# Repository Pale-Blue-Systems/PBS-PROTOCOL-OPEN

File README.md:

# Pale Blue Systems – Open Communication Standards

This repository contains the **open communication standards stewarded by the Pale Blue Systems Foundation (PBSF)**: the PBS protocol specifications, their conformance profiles, the governance documents, and the alignment and traceability records that relate PBS to external sources.

The standards in this repository define a shared **mission-semantic interoperability language** that allows spacecraft, rovers, habitats, autonomous systems, and ground applications to preserve mission meaning, authority, service intent, priority, freshness, security requirements, and PNT context across heterogeneous networks and independently operated service providers.

The PBS specifications define a fixed 44-byte message envelope and a set of optional extensions. Together they carry mission semantics with the data: source identity, priority, timestamp and lifetime, Service Intent, authority context, security profile and PNT context. The specifications define the same semantics over IP, BPv7 and mission-specific links and across independently operated service providers.

---

## Context and Intent

Pale Blue Systems publishes these standards in anticipation of a future space environment that includes **multiple space agencies, commercial operators, scientific missions, private infrastructure, and long-lived off-Earth systems operating concurrently**.

PBS addresses an operating environment in which space agencies, commercial operators and science missions run independently built systems that exchange data over shared relays and networks. For the Moon, the LunaNet Interoperability Specification (LNIS V005, NASA, ESA and JAXA, 29 January 2025) describes LunaNet as a network of cooperating networks on which LunaNet Service Providers deliver communications, PNT and other services, and expects user needs to be met by a combination of interoperable providers (LNIS V005 Preface and Section 1).

This repository establishes a durable mission-semantic interoperability standard for the multi-provider lunar, cislunar, planetary, and deep-space operating environment. It makes interoperability, authority, service intent, and coordination requirements **explicit and addressable early**, before architectural assumptions become embedded in deployed infrastructure.

Additional context on why this work is published now, and the long-term architectural motivations behind it, is available in [`WHY-NOW.md`](WHY-NOW.md).

---

## Why This Repository Exists

As space operations move toward sustained lunar presence, cislunar infrastructure, and Mars exploration, missions increasingly depend on distributed systems operating across:

- long and variable communication delays
- intermittent or scheduled connectivity
- multiple independent authorities and vendors
- human-rated, safety-critical environments

Under these conditions, data must be stored and forwarded between contacts, and its meaning, priority and authority must survive the transfer between organizations.

Strategic analysis has formally identified communications, networking, and coordination as critical technology shortfalls for future exploration architectures, including the need for systems that operate reliably across deep-space and planetary environments.

PBSF exists to steward open standards that directly address these conditions.

NASA's *FY26 Civil Space Shortfall Prioritization* (Space Technology Mission Directorate, May 2026) includes four need statements that PBS v1.4 traces to:

| Need ID | Need statement |
|---|---|
| 13.09 | “Provide advanced networking needed for multi-spacecraft responsive space operations.” |
| 15.01 | “Provide scalable, reliable surface-to-surface communications between assets on the lunar surface that is usable by all participating elements.” |
| 15.03 | “Achieve safe, efficient human-robot interactions for exploration missions, secure command and control over high-latency, bandwidth-limited networks, or implement reliable automated safing sequences.” |
| 24.05 | “Develop a lunar position, navigation, and timing architecture capable of scaling to long term operational needs.” |

Source: <https://www.nasa.gov/wp-content/uploads/2026/05/fy26-civil-space-shortfall-prioritization.pdf>. The requirements PBS derives from them are in [`PBS-TRACE-NASA-FY26-01`](PBS-ALIGNMENT-LIB/PBS-TRACE-NASA-FY26-01.md).

---

## What This Repository Contains

### Specifications

[`PBS-RFC-LIB/`](PBS-RFC-LIB/) contains 19 specifications. PBS Core comprises four specifications with Status Core. A PBS Core conformant implementation implements PBS-ENV-01, PBS-PRIO-01 and PBS-SEC-A-01 (PBS-CONFORMANCE-01 Section 3) and meets the further MUST requirements of PBS-CONFORMANCE-01 Sections 4–9 and 12. The remaining specifications are optional extensions, interoperability and conformance profiles, and governance.

### Reference Implementation

The PBS_LINK Python SDK (<https://github.com/Pale-Blue-Systems/PBS_LINK>, distribution `pbs-link` 0.1.3, import package `PBS_LINK`) implements the PBS-ENV-01 v1.3 envelope. It is maintained in its own repository.

### Hardware Reference Designs

[`PBS-HW-LIB/`](PBS-HW-LIB/) holds open reference designs for hardware that carries PBS traffic: a swappable surface communication module (PBS-HW-SCM-01) and a master device identity tag that can be fitted to any unit (PBS-HW-ID-01). They are informational and do not affect PBS conformance.

### Governance and Alignment

[`PBS-OPEN-STANDARD.md`](PBS-OPEN-STANDARD.md) and [`PBS-GOV-01`](PBS-RFC-LIB/PBS-GOV-01.md) define the stewardship and change process. [`PBS-ALIGNMENT-LIB/`](PBS-ALIGNMENT-LIB/) holds the alignment documents and the NASA FY26 traceability matrix.

---

## Architectural Context

PBS operates at the boundary between mission applications and network services.

```text
Mission Applications
(Rovers, Landers, Habitats, Robots, Ops Software)
          │
          ▼
Pale Blue Systems Open Standards
(Mission Semantics, Service Intent, Authority,
 Security Requirements, PNT Context)
          │
          ▼
Interoperable Network Services
(LunaNet, IP, BPv7, BPSec, CCSDS)
          │
          ▼
Provider / Link Infrastructure
(LNSPs, Relays, RF, Optical, 3GPP, Wi-Fi, Ground)
```

PBS envelopes are user-application data to the network services below them (PBS-LNIS-01 Section 2). PBS-LNIS-REQ-007 requires provider transitions to preserve Source ID, authority context, priority, Service Intent and protected application payload.

---

## Relationship to DTN and BPv7

PBS operates over IP, over BPv7, or through a gateway that selects between them (PBS-LNIS-01 Sections 2 and 4). Two optional specifications define carriage over BPv7. Neither supersedes the other. PBS-DTN-MAP-01 references PBS-DTN-MAP-02 Section 4 for the lifetime bound and Section 5 for the mapping profile of priority-based network treatment.

- **PBS-DTN-MAP-01** (v1.5) defines a gateway translation between PBS-native domains and DTN domains. Each PBS envelope maps to exactly one bundle (Section 5.1). The complete envelope, 44-byte header and payload, is placed unmodified in a single BPv7 payload block (Section 6.2). The bundle lifetime does not exceed the time remaining until the envelope expires, and an envelope with TTL 0 takes the gateway's documented no-expiry lifetime unless a PBS-DTN-MAP-02 Section 4 finite limit applies (Sections 6.1 and 6.1.1). The gateway's bundle protocol agent assigns the creation timestamp (Section 6.1). No primary block field carries priority; a gateway that requests network treatment covers all five priority classes and documents the mechanism in a mapping profile (Section 6.3). Source IDs map deterministically to endpoint identifiers (Section 8).
- **PBS-DTN-MAP-02** (v1.5) defines carriage of v1.4 mission semantics over BPv7 for gateways and endpoints. One PBS protocol data unit SHOULD map to one BP application data unit (Section 2). Bundle lifetime SHALL be bounded by the remaining PBS deadline or expiry; when no finite limit applies it is the no-expiry lifetime documented in the mapping profile (Section 4). The adapter preserves PBS priority unchanged; network treatment is selected through BP QoS mechanisms and provider policy (Section 5). Section 6 maps Service Intent values to BPv7 adapter behavior.

PBS-CONFORMANCE-01 Section 3.1 lists both PBS-DTN-MAP-01 and PBS-DTN-MAP-02 as optional. PBS-ENV-01, PBS-ADDR-01 and PBS-ROUTE-01 reference PBS-DTN-MAP-01. PBS-DTN-MAP-01, PBS-SVC-01, PBS-SEC-B-01, PBS-LNIS-01, PBS-QOS-MAP-01, PBS-CONFORMANCE-02 and the NASA FY26 traceability matrix reference PBS-DTN-MAP-02.

---

## External Alignment

Each alignment document identifies its external sources, summarizes what they state, and maps those statements to PBS specification sections. No source names PBS, and no alignment claims endorsement.

| Alignment ID | Source | Identifier |
| :--- | :--- | :--- |
| [PBS-ALIGN-NASA-LCRNS-02](PBS-ALIGNMENT-LIB/PBS-ALIGN-NASA-LCRNS-02.md) | NASA STMD, *FY26 Civil Space Shortfall Prioritization* (2026); NASA, ESA and JAXA, *LunaNet Interoperability Specification*, V005 (2025) | [FY26 PDF](https://www.nasa.gov/wp-content/uploads/2026/05/fy26-civil-space-shortfall-prioritization.pdf), [LNIS V005 PDF](https://www.nasa.gov/wp-content/uploads/2025/02/lunanet-interoperability-specification-v5-baseline.pdf) |
| [PBS-ALIGN-NASA-LCRNS-01](PBS-ALIGNMENT-LIB/PBS-ALIGN-NASA-LCRNS-01.md) | Esper, Heckler, Verville and Ryden, “NASA’s Lunar Communications Relay and Navigation Systems (LCRNS)”, SpaceOps 2025 | [NTRS 20250003321](https://ntrs.nasa.gov/citations/20250003321) |
| [PBS-ALIGN-IEEE-AEROCONF-ONBOARD-2025-01](PBS-ALIGNMENT-LIB/PBS-ALIGN-IEEE-AEROCONF-ONBOARD-2025-01.md) | Verville and Eddy, “Onboard Processing for LunaNet Data Services”, 2025 IEEE Aerospace Conference | doi:10.1109/AERO63441.2025.11068727 |
| [PBS-ALIGN-IEEE-AEROCONF-2025-01](PBS-ALIGNMENT-LIB/PBS-ALIGN-IEEE-AEROCONF-2025-01.md) | Templin et al., “High Performance DTN Using Larger Packets and Kernel Resident Convergence Layers”, 2025 IEEE Aerospace Conference | doi:10.1109/AERO63441.2025.11068517 |
| [PBS-ALIGN-CARBONARA-TNTN-01](PBS-ALIGNMENT-LIB/PBS-ALIGN-CARBONARA-TNTN-01.md) | Carbonara et al., “Hands-On Solutions for Testing Integrated Terrestrial and Non-Terrestrial Networks: A Comprehensive Survey”, *IEEE Open Journal of the Communications Society*, 2025 | doi:10.1109/OJCOMS.2025.3646364 |
| [PBS-ALIGN-NTONTIN-6G-01](PBS-ALIGNMENT-LIB/PBS-ALIGN-NTONTIN-6G-01.md) | Ntontin et al., “A Vision, Survey, and Roadmap Toward Space Communications in the 6G and Beyond Era”, *Proceedings of the IEEE*, 2025 | doi:10.1109/JPROC.2024.3512934 |
| [PBS-ALIGN-SPJ-LEO-2022-01](PBS-ALIGNMENT-LIB/PBS-ALIGN-SPJ-LEO-2022-01.md) | Zhang et al., “LEO Mega Constellations: Review of Development, Impact, Surveillance, and Governance”, *Space: Science & Technology*, 2022 | doi:10.34133/2022/9865174 |
| [PBS-ALIGN-TF-GOVERNANCE-2024-01](PBS-ALIGNMENT-LIB/PBS-ALIGN-TF-GOVERNANCE-2024-01.md) | Beaumier, Couette and Morin, “Hybrid Organisations and Governance Systems: The Case of the European Space Agency”, *Journal of European Public Policy*, 2025 | doi:10.1080/13501763.2024.2325647 |

[PBS-ALIGN-INDEX-01](PBS-ALIGNMENT-LIB/PBS-ALIGN-INDEX-01.md) summarizes each alignment. [PBS-TRACE-NASA-FY26-01](PBS-ALIGNMENT-LIB/PBS-TRACE-NASA-FY26-01.md) traces 19 PBS requirements to the FY26 need statements, LNIS V005 and RFC 9171.

---

## External Alignment & Validation

The Pale Blue Systems Open Standard is explicitly aligned with authoritative, peer-reviewed architectures from major space agencies and technical bodies.

| Alignment ID | External Source | Domain |
| :--- | :--- | :--- |
| **PBS-ALIGN-NASA-LCRNS-01** | NASA LCRNS (Esper, 2025) | Lunar & Cislunar Networking |
| **PBS-ALIGN-IEEE-AEROCONF-2025** | IEEE Aerospace Conference | Space Network Architecture |
| **PBS-ALIGN-IEEE-TNTN-2025** | IEEE ComSoc | Integrated T/NTN Networks |

---

## Open Standards and Stewardship

PBSF is intentionally structured as a neutral foundation stewarding open standards and reference specifications.

- The specifications are public under the Apache License 2.0.
- PBS-GOV-01 Sections 2 and 3 separate stewardship of the specifications from commercial implementation.
- Changes to PBS Core follow the RFC lifecycle of PBS-GOV-01 Section 5. A backward-incompatible change requires a new major version, except a corrective change, which leaves the wire format unchanged and is released in a patch or minor version with migration guidance where needed (PBS-GOV-01 Sections 5.2 and 6).
- Implementations may extend PBS above the protocol layer. Proprietary extensions are not PBS Core (PBS-GOV-01 Section 7).
- Commercial products and mission systems may implement or extend the standards without altering the core language.

This model enables adoption across civil, commercial, and international space programs while allowing innovation and competition above the protocol layer.

---

## Repository Structure

```text
/
├── README.md
├── WHY-NOW.md                              → Reasons for publishing now
├── PBS-OPEN-STANDARD.md                    → Open standard scope and stewardship model
├── PBS-PROTOCOL-CHANGELOG.md               → Release history
├── PBS-COMMERCIAL-DEVELOPERS-GUIDE.md      → Guide for commercial implementers
├── PBS-REFERENCES-RESOURCES.md             → External references
├── PBS-REFERENCES-SOLAR-SYSTEM-INTERNET.md → IPNSIG Solar System Internet report and PBS-ALIGN-SSIAG-01
├── CONTRIBUTING.md, CLA.md, TRADEMARK-USAGE-POLICY.md, LICENSE
├── PRESS/                                  → Press releases
├── PBS-ALIGNMENT-LIB/                      → Alignment documents and NASA FY26 traceability
│   ├── PBS-ALIGN-INDEX-01.md               → Alignment Index
│   ├── PBS-ALIGN-NASA-LCRNS-01.md          → NASA LCRNS (Esper et al., SpaceOps 2025)
│   ├── PBS-ALIGN-NASA-LCRNS-02.md          → NASA LCRNS, LunaNet, and FY26 Civil Space Shortfalls
│   ├── PBS-ALIGN-IEEE-AEROCONF-2025-01.md  → High-Performance DTN Convergence Layers (Templin et al.)
│   ├── PBS-ALIGN-IEEE-AEROCONF-ONBOARD-2025-01.md → Onboard Processing for LunaNet Data Services (Verville and Eddy)
│   ├── PBS-ALIGN-CARBONARA-TNTN-01.md      → Integrated Terrestrial and Non-Terrestrial Network Testbeds
│   ├── PBS-ALIGN-NTONTIN-6G-01.md          → Space Communications in the 6G and Beyond Era
│   ├── PBS-ALIGN-SPJ-LEO-2022-01.md        → LEO Mega Constellations
│   ├── PBS-ALIGN-TF-GOVERNANCE-2024-01.md  → Space Governance and Hybrid Organisations
│   ├── PBS-ALIGN-ASSIGNMENT-NASA-FY26-01.md → NASA FY26 / LunaNet Alignment Assignment
│   └── PBS-TRACE-NASA-FY26-01.md           → NASA FY26 Requirements Traceability Matrix
└── PBS-RFC-LIB/                            → Protocol specifications
    ├── PBS-ENV-01.md                       → Core Message Envelope
    ├── PBS-ADDR-01.md                      → Addressing and Identification
    ├── PBS-MUX-01.md                       → Payload Multiplexing and Semantic Framing
    ├── PBS-PRIO-01.md                      → Priority Classification and Deterministic Handling
    ├── PBS-SEC-A-01.md                     → Integrity Verification and Security Boundaries
    ├── PBS-POS-01.md                       → Position and Presence Signaling
    ├── PBS-CAPS-01.md                      → Capability Advertisement and Discovery
    ├── PBS-ROUTE-01.md                     → Routing and Forwarding Semantics
    ├── PBS-DTN-MAP-01.md                   → Mapping to Delay/Disruption Tolerant Networking (DTN)
    ├── PBS-CONFORMANCE-01.md               → Conformance, Interoperability, and Mandatory Baselines
    ├── PBS-SVC-01.md                       → Mission Service Intent
    ├── PBS-AUTH-01.md                      → Authority and Scope Context
    ├── PBS-SEC-B-01.md                     → Authenticated Mission Messaging
    ├── PBS-PNT-CTX-01.md                   → Position, Navigation, and Timing Context
    ├── PBS-LNIS-01.md                      → LunaNet Application Alignment Profile
    ├── PBS-DTN-MAP-02.md                   → Mapping to BPv7 Delay/Disruption Tolerant Networking
    ├── PBS-QOS-MAP-01.md                   → Mission Intent to Network Treatment Mapping
    ├── PBS-CONFORMANCE-02.md               → NASA/LunaNet Alignment Conformance and Verification Profile
    └── PBS-GOV-01.md                       → Governance, Stewardship, and Evolution of the PBS Open Standard
```

---

### Quick Links

| Document | Title | Version | Status |
| ------- | ----------- | ---: | ----------- |
| [PBS-OPEN-STANDARD.md](PBS-OPEN-STANDARD.md) | Scope, Stewardship, and Open Standard Model | — | Informational |
| [PBS-ENV-01](PBS-RFC-LIB/PBS-ENV-01.md) | Core Message Envelope | 1.5 | Core |
| [PBS-PRIO-01](PBS-RFC-LIB/PBS-PRIO-01.md) | Priority Classification and Deterministic Handling | 1.4 | Core |
| [PBS-SEC-A-01](PBS-RFC-LIB/PBS-SEC-A-01.md) | Integrity Verification and Security Boundaries | 1.5 | Core |
| [PBS-CONFORMANCE-01](PBS-RFC-LIB/PBS-CONFORMANCE-01.md) | Conformance, Interoperability, and Mandatory Baselines | 1.5 | Core |
| [PBS-ADDR-01](PBS-RFC-LIB/PBS-ADDR-01.md) | Addressing and Identification | 1.3 | Optional Extension |
| [PBS-MUX-01](PBS-RFC-LIB/PBS-MUX-01.md) | Payload Multiplexing and Semantic Framing | 1.4 | Optional Extension |
| [PBS-POS-01](PBS-RFC-LIB/PBS-POS-01.md) | Position and Presence Signaling | 1.4 | Optional Extension |
| [PBS-CAPS-01](PBS-RFC-LIB/PBS-CAPS-01.md) | Capability Advertisement and Discovery | 1.3 | Optional Extension |
| [PBS-ROUTE-01](PBS-RFC-LIB/PBS-ROUTE-01.md) | Routing and Forwarding Semantics | 1.5 | Optional |
| [PBS-DTN-MAP-01](PBS-RFC-LIB/PBS-DTN-MAP-01.md) | Mapping to Delay/Disruption Tolerant Networking (DTN) | 1.5 | Optional (Interoperability) |
| [PBS-SVC-01](PBS-RFC-LIB/PBS-SVC-01.md) | Mission Service Intent | 1.4 | Optional Extension |
| [PBS-AUTH-01](PBS-RFC-LIB/PBS-AUTH-01.md) | Authority and Scope Context | 1.4 | Optional Extension; Required by PBS-SEC-B command profile |
| [PBS-SEC-B-01](PBS-RFC-LIB/PBS-SEC-B-01.md) | Authenticated Mission Messaging | 1.5 | Optional Security Profile |
| [PBS-PNT-CTX-01](PBS-RFC-LIB/PBS-PNT-CTX-01.md) | Position, Navigation, and Timing Context | 1.4 | Optional Extension |
| [PBS-LNIS-01](PBS-RFC-LIB/PBS-LNIS-01.md) | LunaNet Application Alignment Profile | 1.4 | Optional Interoperability Profile |
| [PBS-DTN-MAP-02](PBS-RFC-LIB/PBS-DTN-MAP-02.md) | Mapping to BPv7 Delay/Disruption Tolerant Networking | 1.5 | Optional Interoperability Profile |
| [PBS-QOS-MAP-01](PBS-RFC-LIB/PBS-QOS-MAP-01.md) | Mission Intent to Network Treatment Mapping | 1.4 | Optional Adapter Profile |
| [PBS-CONFORMANCE-02](PBS-RFC-LIB/PBS-CONFORMANCE-02.md) | NASA/LunaNet Alignment Conformance and Verification Profile | 1.5 | Optional Conformance Profile |
| [PBS-GOV-01](PBS-RFC-LIB/PBS-GOV-01.md) | Governance, Stewardship, and Evolution of the PBS Open Standard | 1.5 | Informational (Normative Governance) |

---

## Status

The current release is PBS v1.5.0 (2026-10-06), a corrective release (PBS-GOV-01 Section 5.2) that resolves the six known issues recorded in PBS v1.4.1. PBS v1.5.0 does not change the wire format; it changes relay, gateway and BPv7 mapping requirements, and [`PBS-PROTOCOL-CHANGELOG.md`](PBS-PROTOCOL-CHANGELOG.md) gives the migration.

Each specification carries its own version, the minor release in which it last changed. Documents unchanged since v1.3 remain at 1.3 and documents unchanged since v1.4 remain at 1.4; an erratum does not change a specification's version. Errata are recorded in the header of each corrected specification (**Errata** line); a specification revised in v1.5.0 records its changes in a **Changes** line. Both are recorded in [`PBS-PROTOCOL-CHANGELOG.md`](PBS-PROTOCOL-CHANGELOG.md). Defects in normative text that v1.5.0 does not correct are listed under [Known issues](PBS-PROTOCOL-CHANGELOG.md#known-issues-not-corrected-in-v150).

The specifications define wire formats and behavior independent of hardware, transport and implementation language. The 44-byte PBS-ENV-01 header structure and PBS Core semantics remain stable for all v1.x releases. A backward-incompatible change requires a new major version, except a corrective change, which leaves the wire format unchanged and is released in a patch or minor version with migration guidance where needed, as in PBS v1.5.0 (PBS-CONFORMANCE-01 Section 12, PBS-GOV-01 Sections 5.2 and 6).

---

## Legal and Governance

### License
The Pale Blue Systems Open Standard and reference implementations are released under the **Apache License 2.0**.  
See [`LICENSE`](LICENSE) for details.

### Intellectual Property & Contribution
To ensure long-term neutrality and availability, all contributions are subject to the Pale Blue Systems Foundation **Contributor License Agreement (CLA)**.  
See [`CLA.md`](CLA.md) for full terms.

### Trademark Usage
"Pale Blue Systems", "PBSF", and the PBS logo are trademarks of the Pale Blue Systems Foundation.  
See [`TRADEMARK-USAGE-POLICY.md`](TRADEMARK-USAGE-POLICY.md) for guidelines.

---

## About the Foundation

The Pale Blue Systems Foundation stewards open, interoperable communication standards to support humanity’s expansion into space through cooperation, reliability, and technical clarity. It stewards the PBS specifications in this repository under the governance model of PBS-GOV-01.

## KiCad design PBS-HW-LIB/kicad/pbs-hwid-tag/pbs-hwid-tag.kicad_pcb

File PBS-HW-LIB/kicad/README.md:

# PBS Hardware Reference Library: KiCad Projects

KiCad projects for the open reference designs of this library. Every part on these boards is a generic placeholder named by the **common type of part that goes there** (for example "Radiation-hardened microcontroller with EDAC", "LTE/NR modem module", "Secure element"). No part numbers and no manufacturers appear. A builder replaces each placeholder footprint with the footprint of the part they choose; the nets, which carry the interconnect the specifications require, do not change.

| Project | Document | Board |
|---|---|---|
| [`pbs-scm-core/`](pbs-scm-core/) | PBS-HW-SCM-01 | Module core board, 92 × 92 mm, shared by the SCM-S and SCM-L shells, with the module half of the host connector on the back. Four schematic sheets: host interface and power; control function, storage, host data; radios and RF; heaters and temperature sensing |
| [`pbs-scm-bay/`](pbs-scm-bay/) | PBS-HW-SCM-01 | Host bay interface board, 112 × 32 mm: the host side of the module connector, the swap-detect loop and the identity-tag connection |
| [`pbs-hwid-tag/`](pbs-hwid-tag/) | PBS-HW-ID-01 | Identity tag, 25 mm round: secure element, contactless front end, antenna coil in copper, wired-interface pads on the back |

## What each project contains

- `<project>.kicad_pro`, `.kicad_sch` (and sub-sheets), `.kicad_pcb`: open in KiCad 8 or 9.
- `PBS_Generic.kicad_sym` and `PBS_Generic.pretty/`: the project's placeholder symbols and footprints, registered in the project's library tables.
- `3d/`: placeholder 3D bodies, coloured by function.
- `output/`:
  - `-schematic.pdf`: the schematics;
  - `-assembly-top.pdf`, `-assembly-bottom.pdf`: board outline, part outlines and a legend of reference to part type;
  - `-labelled-top.png`: top view with part types on the silkscreen;
  - `-3d-top.png`, `-3d-bottom.png`, `-3d-iso.png`: renders with placeholder bodies;
  - `.step`, `.wrl`: 3D models of the board;
  - `-erc.rpt`, `-drc.rpt`: the KiCad electrical and design rule check reports.

## Conventions

| Colour of 3D body | Function |
|---|---|
| Orange | Power path |
| Dark blue | Control function |
| Light blue | Storage |
| Grey | Host and data interfaces |
| Green | Radios |
| Light grey | RF filters, switches and antenna ports |
| Red | Heaters and temperature sensors |
| Purple | Identity |

- **Host connector (core J1, bay J1).** Both halves of the connector of PBS-HW-CON-01, at its true contact positions. Core J1 is the module half on the back of the core board, centred, drawn in the module-face view: hard-gold pads and the two guide-bushing holes. Bay J1 is the bay half: plated holes for the spring contacts and the RF plug, and the two guide-pin holes (A Ø4.00, B Ø3.00). Pad numbers are the contact numbers. The bay 3D model shows the spring contacts at their free heights, coloured by mating order (green 1 chassis, red 2 power, blue 3 data and identity bus, purple 4 detect), the guide pins, and the cover plate (translucent) in its unmated position. In both board views the top edge of the drawing is the module front (+y).
- **Connector geometry.** `tools/connector.py` holds every connector dimension. The footprints, the 3D models and the drawings in [`../drawings/`](../drawings/) are generated from it.
- **Fit.** Parts marked "Class M only" are omitted from Class H modules. U24 (S-band amplifier) is fitted in SCM-L; JP1 (RF bypass) in SCM-S. U27 (ultra-wideband) is optional and off by default.
- **Not routed.** The placeholders are not routed. The design rule check reports unrouted nets as warnings and passes with no errors; the schematic check passes with no errors or warnings.
- **Antenna coil (tag L1).** Drawn as one copper polygon in a net-tie footprint between COIL_A and COIL_B.

## Regenerating

The projects are generated from one interconnect model:

```sh
sh PBS-HW-LIB/kicad/tools/export.sh
```

This runs `tools/generate.py` (requires KiCad 9 and its Python module), the KiCad checks, every export above, and `tools/connector_drawing.py` (requires matplotlib), which draws the connector sheets. Editing the projects in KiCad directly is also fine; regenerating overwrites them.

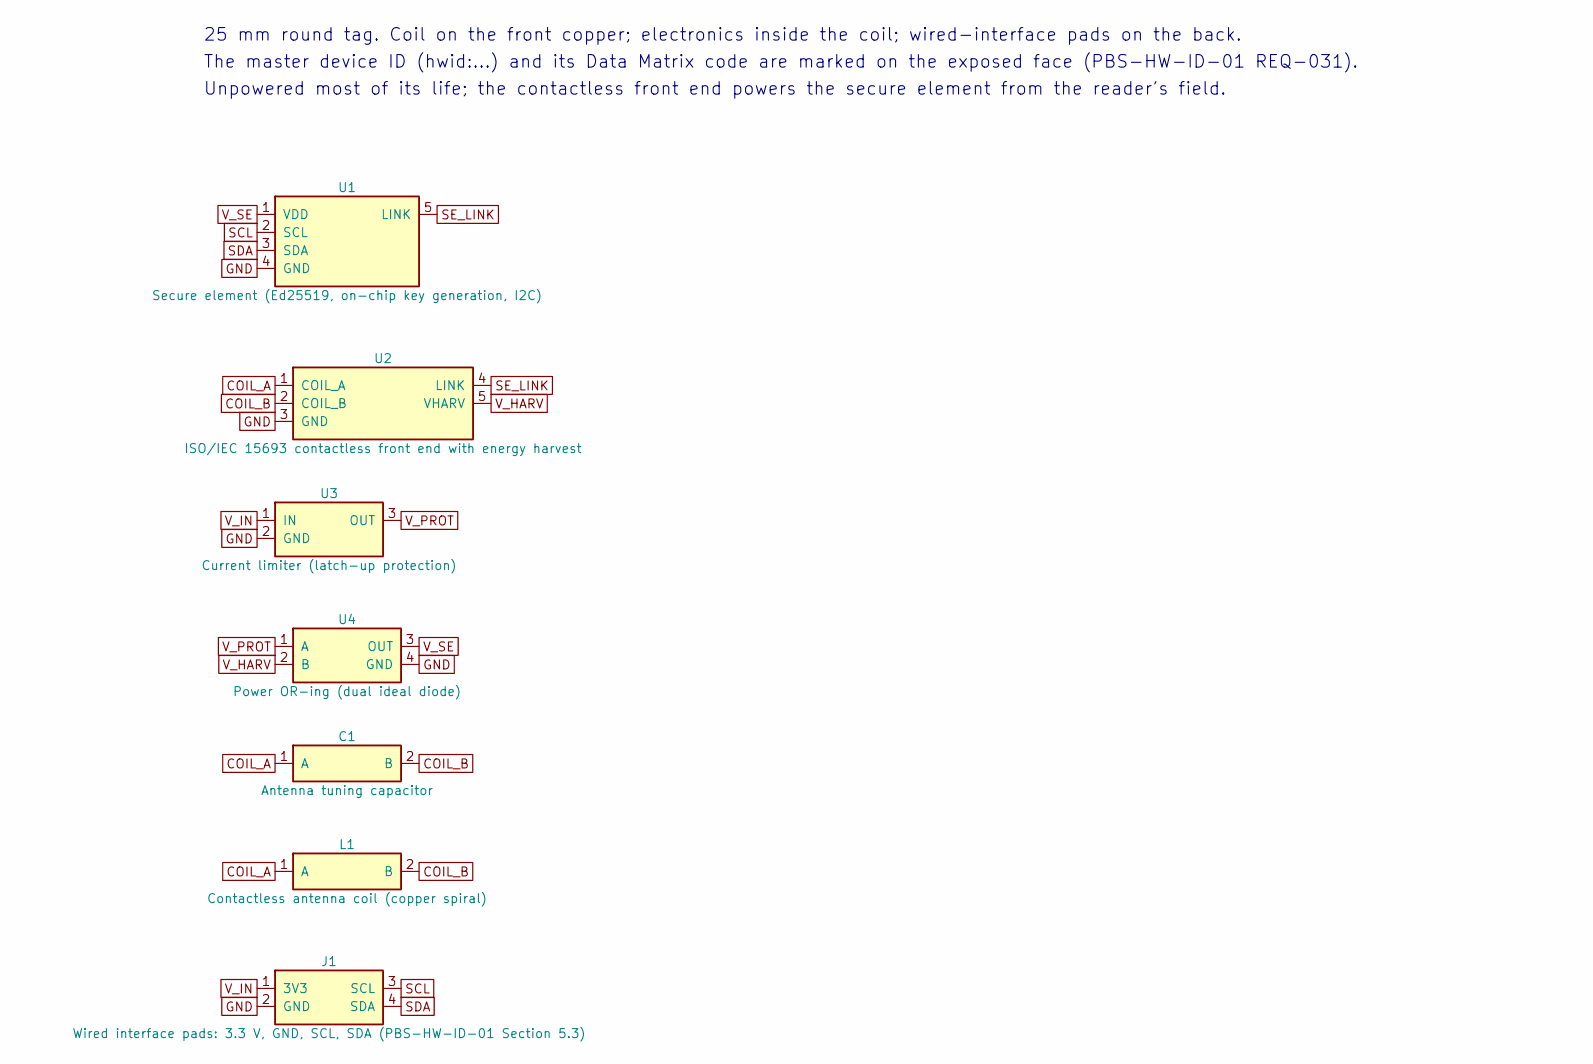
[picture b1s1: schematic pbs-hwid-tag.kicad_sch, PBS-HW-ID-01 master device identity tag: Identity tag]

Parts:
C1: Antenna tuning capacitor; C1_Antenna_tuning_capacitor
J1: Wired interface pads: 3.3 V, GND, SCL, SDA (PBS-H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; J1_Wired_interface_pads_3_3_V_GND_SCL_SDA_PBS_HW_ID_01_Sect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
L1: Contactless antenna coil (copper spiral); L1_Contactless_antenna_coil_copper_spiral
U1: Secure element (Ed25519, on-chip key generation, 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; U1_Secure_element_Ed25519_on_chip_key_generation_I2C
U2: ISO/IEC 15693 contactless front end with energy h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; U2_ISO_IEC_15693_contactless_front_end_with_energy_harvest
U3: Current limiter (latch-up protection); U3_Current_limiter_latch_up_protection
U4: Power OR-ing (dual ideal diode); U4_Power_OR_ing_dual_ideal_diode

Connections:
COIL_A: C1.1 (A), L1.1 (A), U2.1 (COIL_A)
COIL_B: C1.2 (B), L1.2 (B), U2.2 (COIL_B)
GND: J1.2 (GND), U1.4 (GND), U2.3 (GND), U3.2 (GND), U4.4 (GND)
SCL: J1.3 (SCL), U1.2 (SCL)
SDA: J1.4 (SDA), U1.3 (SDA)
SE_LINK: U1.5 (LINK), U2.4 (LINK)
V_HARV: U2.5 (VHARV), U4.2 (B)
V_IN: J1.1 (3V3), U3.1 (IN)
V_PROT: U3.3 (OUT), U4.1 (A)
V_SE: U1.1 (VDD), U4.3 (OUT)

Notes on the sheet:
25 mm round tag. Coil on the front copper; electronics inside the coil; wired-interface pads on the back.
The master device ID (hwid:...) and its Data Matrix code are marked on the exposed face (PBS-HW-ID-01 REQ-031).
Unpowered most of its life; the contactless front end powers the secure element from the reader's field.

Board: 2 copper layers, 7 parts (1 on the bottom side), 10 nets, no tracks yet.

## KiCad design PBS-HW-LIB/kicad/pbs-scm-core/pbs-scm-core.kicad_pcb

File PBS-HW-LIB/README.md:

# PBS Hardware Reference Library

Open reference designs for hardware that carries PBS traffic. They are informational: they are not part of PBS Core and do not affect any PBS conformance claim (PBS-CONFORMANCE-01).

| Document | Title | Status | Version |
|---|---|---|---|
| [PBS-HW-SCM-01](PBS-HW-SCM-01.md) | Surface Communication Module: Open Reference Design | Draft Reference Design | 0.3 |
| [PBS-HW-CON-01](PBS-HW-CON-01.md) | Module Host Connector: Open Reference Design | Draft Reference Design | 0.3 |
| [PBS-HW-ID-01](PBS-HW-ID-01.md) | Master Device Identity Tag: Open Reference Design | Draft Reference Design | 0.2 |

These documents let anyone build the hardware and make independently built parts work together. They specify interoperability requirements, marked [I], which must be met exactly (connectors, contacts, bands, protocols, formats, behaviour), and minimum performance, marked [P], which builders may exceed. They name no components or manufacturers. Normative statements bind only implementations that claim to follow a document.

KiCad projects for these designs (schematics, boards, renders and 3D models, with generic part-type placeholders) are in [`kicad/`](kicad/). Dimensioned drawings of the connector are in [`drawings/`](drawings/).

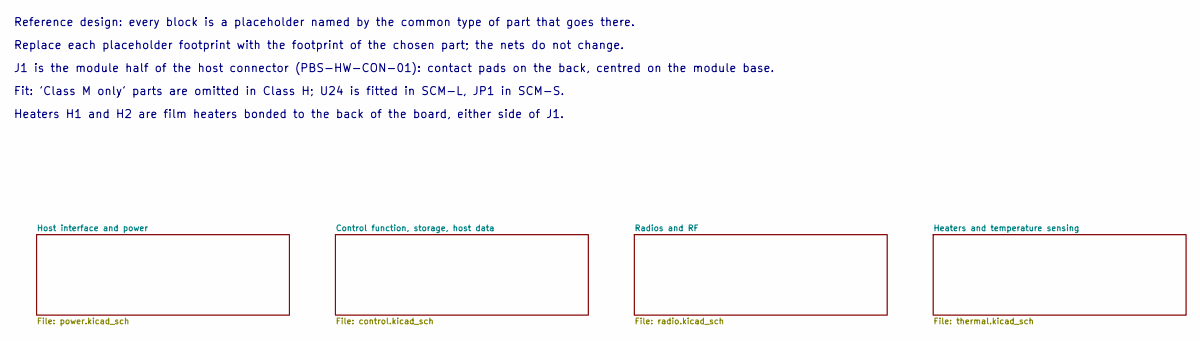
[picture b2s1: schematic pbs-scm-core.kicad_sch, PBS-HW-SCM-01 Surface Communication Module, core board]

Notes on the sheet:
Reference design: every block is a placeholder named by the common type of part that goes there.
Replace each placeholder footprint with the footprint of the chosen part; the nets do not change.
J1 is the module half of the host connector (PBS-HW-CON-01): contact pads on the back, centred on the module base.
Fit: 'Class M only' parts are omitted in Class H; U24 is fitted in SCM-L, JP1 in SCM-S.
Heaters H1 and H2 are film heaters bonded to the back of the board, either side of J1.

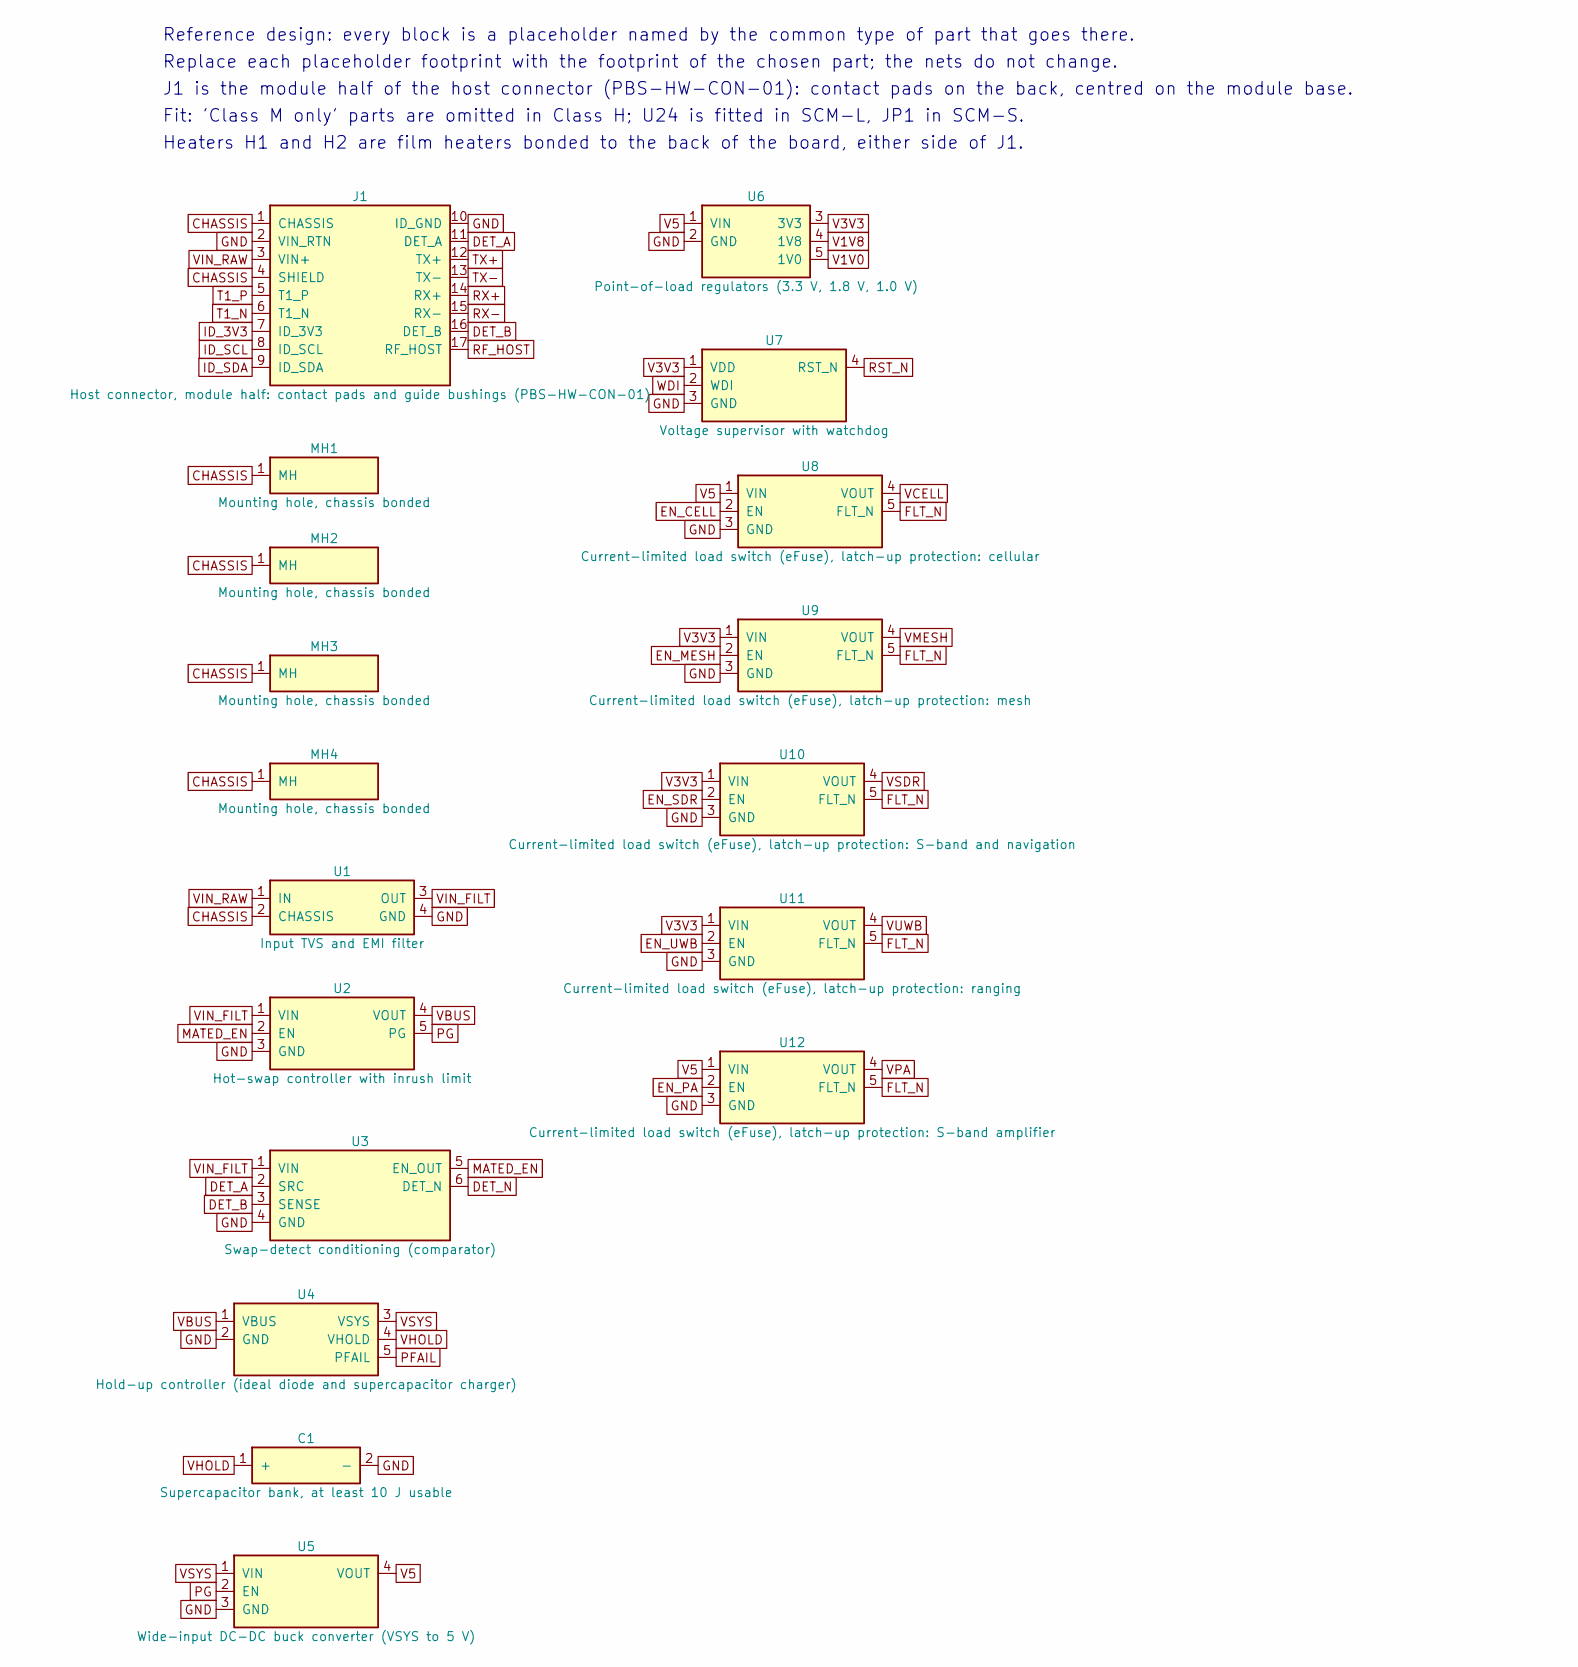
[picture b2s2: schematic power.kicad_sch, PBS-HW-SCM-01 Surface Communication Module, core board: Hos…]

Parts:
C1: Supercapacitor bank, at least 10 J usable; C1_Supercapacitor_bank_at_least_10_J_usable
J1: Host connector, module half: contact pads and gui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; J1_Host_connector_module_half_contact_pads_and_guide_bushin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
MH1: Mounting hole, chassis bonded; MH1_Mounting_hole_chassis_bonded
MH2: Mounting hole, chassis bonded; MH2_Mounting_hole_chassis_bonded
MH3: Mounting hole, chassis bonded; MH3_Mounting_hole_chassis_bonded
MH4: Mounting hole, chassis bonded; MH4_Mounting_hole_chassis_bonded
U1: Input TVS and EMI filter; U1_Input_TVS_and_EMI_filter
U2: Hot-swap controller with inrush limit; U2_Hot_swap_controller_with_inrush_limit
U3: Swap-detect conditioning (comparator); U3_Swap_detect_conditioning_comparator
U4: Hold-up controller (ideal diode and supercapacito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; U4_Hold_up_controller_ideal_diode_and_supercapacitor_charger
U5: Wide-input DC-DC buck converter (VSYS to 5 V); U5_Wide_input_DC_DC_buck_converter_VSYS_to_5_V
U6: Point-of-load regulators (3.3 V, 1.8 V, 1.0 V); U6_Point_of_load_regulators_3_3_V_1_8_V_1_0_V
U7: Voltage supervisor with watchdog; U7_Voltage_supervisor_with_watchdog
U8: Current-limited load switch (eFuse), latch-up pro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; U8_Current_limited_load_switch_eFuse_latch_up_protection_ce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
U9: Current-limited load switch (eFuse), latch-up pro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; U9_Current_limited_load_switch_eFuse_latch_up_protection_me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
U10: Current-limited load switch (eFuse), latch-up pro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; U10_Current_limited_load_switch_eFuse_latch_up_protection_S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
U11: Current-limited load switch (eFuse), latch-up pro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; U11_Current_limited_load_switch_eFuse_latch_up_protection_r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
U12: Current-limited load switch (eFuse), latch-up pro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; U12_Current_limited_load_switch_eFuse_latch_up_protection_S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

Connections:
CHASSIS: J1.1 (CHASSIS), J1.4 (SHIELD), MH1.1, MH2.1, MH3.1, MH4.1, U1.2 (CHASSIS)
DET_A: J1.11 (DET_A), U3.2 (SRC)
DET_B: J1.16 (DET_B), U3.3 (SENSE)
DET_N: U3.6 (DET_N); also elsewhere on the board
EN_CELL: U8.2 (EN); also elsewhere on the board
EN_MESH: U9.2 (EN); also elsewhere on the board
EN_PA: U12.2 (EN); also elsewhere on the board
EN_SDR: U10.2 (EN); also elsewhere on the board
EN_UWB: U11.2 (EN); also elsewhere on the board
FLT_N: U8.5 (FLT_N), U9.5 (FLT_N), U10.5 (FLT_N), U11.5 (FLT_N), U12.5 (FLT_N); also elsewhere on the board
GND: C1.2 (-), J1.2 (VIN_RTN), J1.10 (ID_GND), U1.4 (GND), U2.3 (GND), U3.4 (GND), U4.2 (GND), U5.3 (GND), U6.2 (GND), U7.3 (GND), U8.3 (GND), U9.3 (GND), U10.3 (GND), U11.3 (GND), U12.3 (GND); also elsewhere on the board
ID_3V3: J1.7 (ID_3V3); also elsewhere on the board
ID_SCL: J1.8 (ID_SCL); also elsewhere on the board
ID_SDA: J1.9 (ID_SDA); also elsewhere on the board
MATED_EN: U2.2 (EN), U3.5 (EN_OUT)
PFAIL: U4.5 (PFAIL); also elsewhere on the board
PG: U2.5 (PG), U5.2 (EN); also elsewhere on the board
RF_HOST: J1.17 (RF_HOST); also elsewhere on the board
RST_N: U7.4 (RST_N); also elsewhere on the board
RX+: J1.14 (RX+)
RX-: J1.15 (RX-)
T1_N: J1.6 (T1_N); also elsewhere on the board
T1_P: J1.5 (T1_P); also elsewhere on the board
TX+: J1.12 (TX+)
TX-: J1.13 (TX-)
V1V0: U6.5 (1V0); also elsewhere on the board
V1V8: U6.4 (1V8); also elsewhere on the board
V3V3: U6.3 (3V3), U7.1 (VDD), U9.1 (VIN), U10.1 (VIN), U11.1 (VIN); also elsewhere on the board
V5: U5.4 (VOUT), U6.1 (VIN), U8.1 (VIN), U12.1 (VIN)
VBUS: U2.4 (VOUT), U4.1 (VBUS)
VCELL: U8.4 (VOUT); also elsewhere on the board
VHOLD: C1.1 (+), U4.4 (VHOLD)
VIN_FILT: U1.3 (OUT), U2.1 (VIN), U3.1 (VIN)
VIN_RAW: J1.3 (VIN+), U1.1 (IN)
VMESH: U9.4 (VOUT); also elsewhere on the board
VPA: U12.4 (VOUT); also elsewhere on the board
VSDR: U10.4 (VOUT); also elsewhere on the board
VSYS: U4.3 (VSYS), U5.1 (VIN); also elsewhere on the board
VUWB: U11.4 (VOUT); also elsewhere on the board
WDI: U7.2 (WDI); also elsewhere on the board

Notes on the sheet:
Reference design: every block is a placeholder named by the common type of part that goes there.
Replace each placeholder footprint with the footprint of the chosen part; the nets do not change.
J1 is the module half of the host connector (PBS-HW-CON-01): contact pads on the back, centred on the module base.
Fit: 'Class M only' parts are omitted in Class H; U24 is fitted in SCM-L, JP1 in SCM-S.
Heaters H1 and H2 are film heaters bonded to the back of the board, either side of J1.

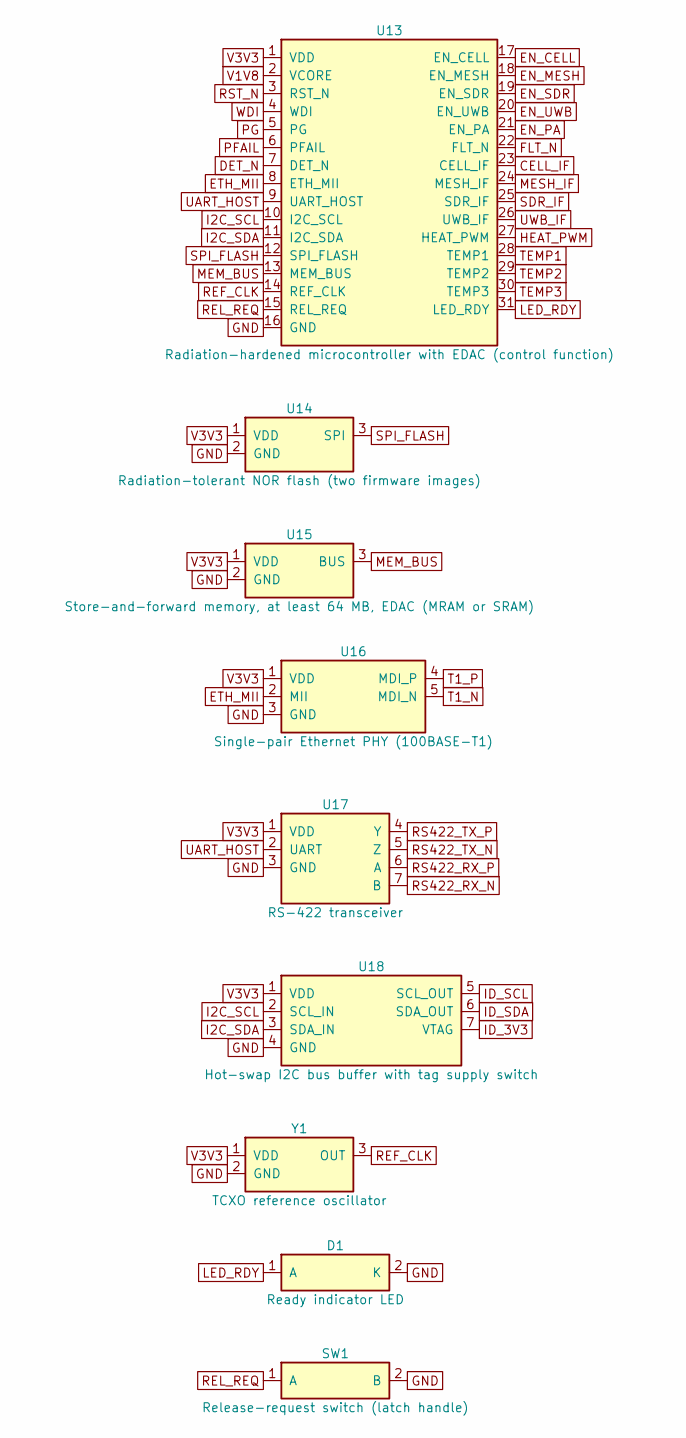
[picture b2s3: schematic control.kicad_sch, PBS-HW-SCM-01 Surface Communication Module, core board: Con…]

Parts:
D1: Ready indicator LED; D1_Ready_indicator_LED
SW1: Release-request switch (latch handle); SW1_Release_request_switch_latch_handle
U13: Radiation-hardened microcontroller with EDAC (con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; U13_Radiation_hardened_microcontroller_with_EDAC_control_fu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
U14: Radiation-tolerant NOR flash (two firmware images); U14_Radiation_tolerant_NOR_flash_two_firmware_images
U15: Store-and-forward memory, at least 64 MB, EDAC (M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; U15_Store_and_forward_memory_at_least_64_MB_EDAC_MRAM_or_SR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
U16: Single-pair Ethernet PHY (100BASE-T1); U16_Single_pair_Ethernet_PHY_100BASE_T1
U17: RS-422 transceiver; U17_RS_422_transceiver
U18: Hot-swap I2C bus buffer with tag supply switch; U18_Hot_swap_I2C_bus_buffer_with_tag_supply_switch
Y1: TCXO reference oscillator; Y1_TCXO_reference_oscillator

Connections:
CELL_IF: U13.23 (CELL_IF); also elsewhere on the board
DET_N: U13.7 (DET_N); also elsewhere on the board
EN_CELL: U13.17 (EN_CELL); also elsewhere on the board
EN_MESH: U13.18 (EN_MESH); also elsewhere on the board
EN_PA: U13.21 (EN_PA); also elsewhere on the board
EN_SDR: U13.19 (EN_SDR); also elsewhere on the board
EN_UWB: U13.20 (EN_UWB); also elsewhere on the board
ETH_MII: U13.8 (ETH_MII), U16.2 (MII)
FLT_N: U13.22 (FLT_N); also elsewhere on the board
GND: D1.2 (K), SW1.2 (B), U13.16 (GND), U14.2 (GND), U15.2 (GND), U16.3 (GND), U17.3 (GND), U18.4 (GND), Y1.2 (GND); also elsewhere on the board
HEAT_PWM: U13.27 (HEAT_PWM); also elsewhere on the board
I2C_SCL: U13.10 (I2C_SCL), U18.2 (SCL_IN)
I2C_SDA: U13.11 (I2C_SDA), U18.3 (SDA_IN)
ID_3V3: U18.7 (VTAG); also elsewhere on the board
ID_SCL: U18.5 (SCL_OUT); also elsewhere on the board
ID_SDA: U18.6 (SDA_OUT); also elsewhere on the board
LED_RDY: D1.1 (A), U13.31 (LED_RDY)
MEM_BUS: U13.13 (MEM_BUS), U15.3 (BUS)
MESH_IF: U13.24 (MESH_IF); also elsewhere on the board
PFAIL: U13.6 (PFAIL); also elsewhere on the board
PG: U13.5 (PG); also elsewhere on the board
REF_CLK: U13.14 (REF_CLK), Y1.3 (OUT); also elsewhere on the board
REL_REQ: SW1.1 (A), U13.15 (REL_REQ)
RS422_RX_N: U17.7 (B)
RS422_RX_P: U17.6 (A)
RS422_TX_N: U17.5 (Z)
RS422_TX_P: U17.4 (Y)
RST_N: U13.3 (RST_N); also elsewhere on the board
SDR_IF: U13.25 (SDR_IF); also elsewhere on the board
SPI_FLASH: U13.12 (SPI_FLASH), U14.3 (SPI)
T1_N: U16.5 (MDI_N); also elsewhere on the board
T1_P: U16.4 (MDI_P); also elsewhere on the board
TEMP1: U13.28 (TEMP1); also elsewhere on the board
TEMP2: U13.29 (TEMP2); also elsewhere on the board
TEMP3: U13.30 (TEMP3); also elsewhere on the board
UART_HOST: U13.9 (UART_HOST), U17.2 (UART)
UWB_IF: U13.26 (UWB_IF); also elsewhere on the board
V1V8: U13.2 (VCORE); also elsewhere on the board
V3V3: U13.1 (VDD), U14.1 (VDD), U15.1 (VDD), U16.1 (VDD), U17.1 (VDD), U18.1 (VDD), Y1.1 (VDD); also elsewhere on the board
WDI: U13.4 (WDI); also elsewhere on the board

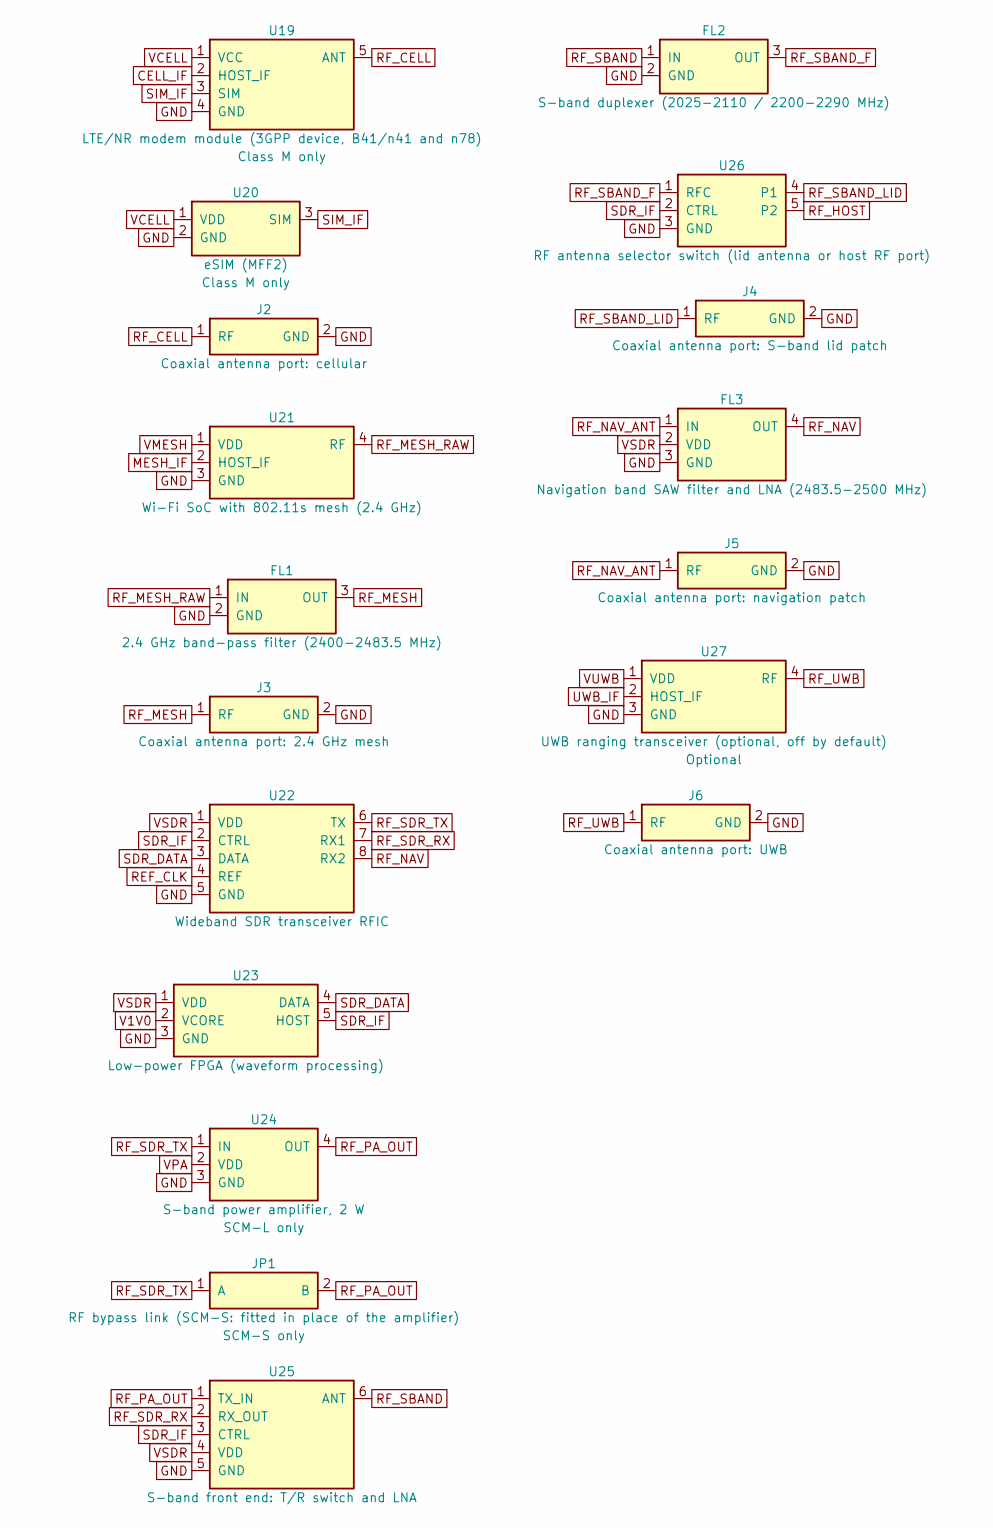
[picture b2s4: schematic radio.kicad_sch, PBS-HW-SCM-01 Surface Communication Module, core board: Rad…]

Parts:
FL1: 2.4 GHz band-pass filter (2400-2483.5 MHz); FL1_2_4_GHz_band_pass_filter_2400_2483_5_MHz
FL2: S-band duplexer (2025-2110 / 2200-2290 MHz); FL2_S_band_duplexer_2025_2110_2200_2290_MHz
FL3: Navigation band SAW filter and LNA (2483.5-2500 M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; FL3_Navigation_band_SAW_filter_and_LNA_2483_5_2500_MHz
J2: Coaxial antenna port: cellular; J2_Coaxial_antenna_port_cellular
J3: Coaxial antenna port: 2.4 GHz mesh; J3_Coaxial_antenna_port_2_4_GHz_mesh
J4: Coaxial antenna port: S-band lid patch; J4_Coaxial_antenna_port_S_band_lid_patch
J5: Coaxial antenna port: navigation patch; J5_Coaxial_antenna_port_navigation_patch
J6: Coaxial antenna port: UWB; J6_Coaxial_antenna_port_UWB
JP1: RF bypass link (SCM-S: fitted in place of the amp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; JP1_RF_bypass_link_SCM_S_fitted_in_place_of_the_amplifier
U19: LTE/NR modem module (3GPP device, B41/n41 and n78); U19_LTE_NR_modem_module_3GPP_device_B41_n41_and_n78
U20: eSIM (MFF2); U20_eSIM_MFF2
U21: Wi-Fi SoC with 802.11s mesh (2.4 GHz); U21_Wi_Fi_SoC_with_802_11s_mesh_2_4_GHz
U22: Wideband SDR transceiver RFIC; U22_Wideband_SDR_transceiver_RFIC
U23: Low-power FPGA (waveform processing); U23_Low_power_FPGA_waveform_processing
U24: S-band power amplifier, 2 W; U24_S_band_power_amplifier_2_W
U25: S-band front end: T/R switch and LNA; U25_S_band_front_end_T_R_switch_and_LNA
U26: RF antenna selector switch (lid antenna or host R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; U26_RF_antenna_selector_switch_lid_antenna_or_host_RF_port
U27: UWB ranging transceiver (optional, off by default); U27_UWB_ranging_transceiver_optional_off_by_default

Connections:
CELL_IF: U19.2 (HOST_IF); also elsewhere on the board
GND: FL1.2 (GND), FL2.2 (GND), FL3.3 (GND), J2.2 (GND), J3.2 (GND), J4.2 (GND), J5.2 (GND), J6.2 (GND), U19.4 (GND), U20.2 (GND), U21.3 (GND), U22.5 (GND), U23.3 (GND), U24.3 (GND), U25.5 (GND), U26.3 (GND), U27.3 (GND); also elsewhere on the board
MESH_IF: U21.2 (HOST_IF); also elsewhere on the board
REF_CLK: U22.4 (REF); also elsewhere on the board
RF_CELL: J2.1 (RF), U19.5 (ANT)
RF_HOST: U26.5 (P2); also elsewhere on the board
RF_MESH: FL1.3 (OUT), J3.1 (RF)
RF_MESH_RAW: FL1.1 (IN), U21.4 (RF)
RF_NAV: FL3.4 (OUT), U22.8 (RX2)
RF_NAV_ANT: FL3.1 (IN), J5.1 (RF)
RF_PA_OUT: JP1.2 (B), U24.4 (OUT), U25.1 (TX_IN)
RF_SBAND: FL2.1 (IN), U25.6 (ANT)
RF_SBAND_F: FL2.3 (OUT), U26.1 (RFC)
RF_SBAND_LID: J4.1 (RF), U26.4 (P1)
RF_SDR_RX: U22.7 (RX1), U25.2 (RX_OUT)
RF_SDR_TX: JP1.1 (A), U22.6 (TX), U24.1 (IN)
RF_UWB: J6.1 (RF), U27.4 (RF)
SDR_DATA: U22.3 (DATA), U23.4 (DATA)
SDR_IF: U22.2 (CTRL), U23.5 (HOST), U25.3 (CTRL), U26.2 (CTRL); also elsewhere on the board
SIM_IF: U19.3 (SIM), U20.3 (SIM)
UWB_IF: U27.2 (HOST_IF); also elsewhere on the board
V1V0: U23.2 (VCORE); also elsewhere on the board
VCELL: U19.1 (VCC), U20.1 (VDD); also elsewhere on the board
VMESH: U21.1 (VDD); also elsewhere on the board
VPA: U24.2 (VDD); also elsewhere on the board
VSDR: FL3.2 (VDD), U22.1 (VDD), U23.1 (VDD), U25.4 (VDD); also elsewhere on the board
VUWB: U27.1 (VDD); also elsewhere on the board

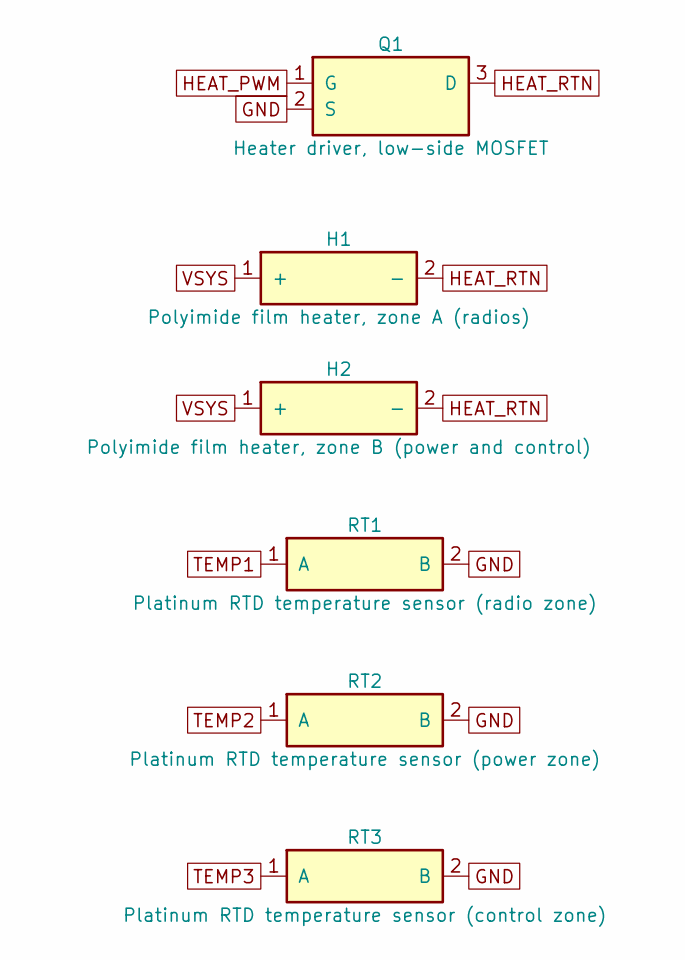
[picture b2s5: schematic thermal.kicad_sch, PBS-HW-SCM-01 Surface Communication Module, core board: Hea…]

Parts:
H1: Polyimide film heater, zone A (radios); H1_Polyimide_film_heater_zone_A_radios
H2: Polyimide film heater, zone B (power and control); H2_Polyimide_film_heater_zone_B_power_and_control
Q1: Heater driver, low-side MOSFET; Q1_Heater_driver_low_side_MOSFET
RT1: Platinum RTD temperature sensor (radio zone); RT1_Platinum_RTD_temperature_sensor_radio_zone
RT2: Platinum RTD temperature sensor (power zone); RT2_Platinum_RTD_temperature_sensor_power_zone
RT3: Platinum RTD temperature sensor (control zone); RT3_Platinum_RTD_temperature_sensor_control_zone

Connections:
GND: Q1.2 (S), RT1.2 (B), RT2.2 (B), RT3.2 (B); also elsewhere on the board
HEAT_PWM: Q1.1 (G); also elsewhere on the board
HEAT_RTN: H1.2 (-), H2.2 (-), Q1.3 (D)
TEMP1: RT1.1 (A); also elsewhere on the board
TEMP2: RT2.1 (A); also elsewhere on the board
TEMP3: RT3.1 (A); also elsewhere on the board
VSYS: H1.1 (+), H2.1 (+); also elsewhere on the board

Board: 4 copper layers, 51 parts (3 on the bottom side), 68 nets, no tracks yet.
